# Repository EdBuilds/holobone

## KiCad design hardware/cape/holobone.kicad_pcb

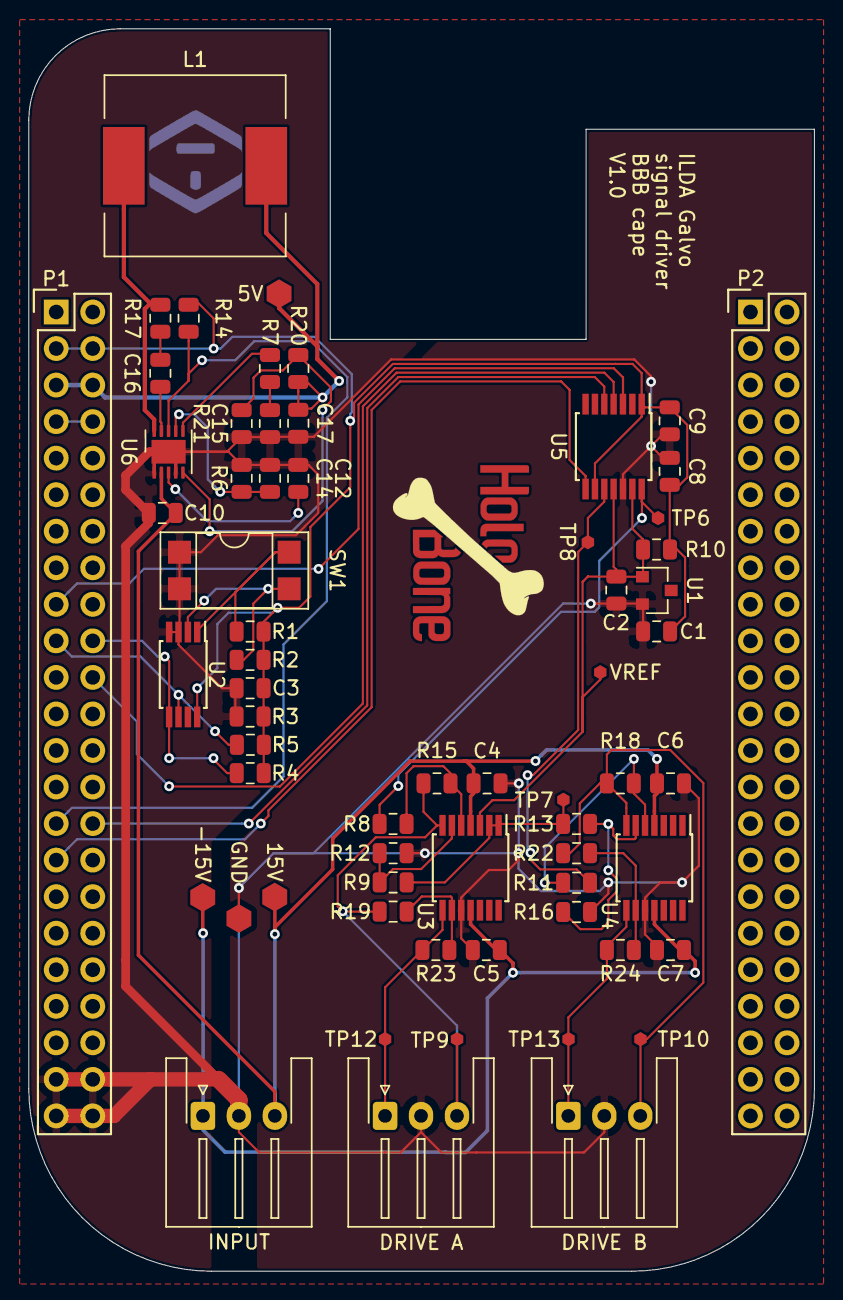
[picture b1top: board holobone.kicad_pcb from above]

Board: 2 copper layers, 54.6 x 86.4 mm, 65 parts (0 on the bottom side), 37 nets.

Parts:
5V, 15V: TestPoint; hex_test_pad_2mm
 : HoloBone_logo12.2x10.5mm
-15V: TestPoint; hex_test_pad_2mm
C1, C2, C3, C4, C5, C6, C7, C9, C16: 0.1uF; C_0805_2012Metric
C8: 4.7uF; C_0805_2012Metric
C10: 10uF; C_0805_2012Metric
C12: 3.3uF; C_0805_2012Metric
C14: 22nF; C_0805_2012Metric
C15: 1000 pF; C_0805_2012Metric
C17: 2.2uF; C_0805_2012Metric
DRIVE A: Conn_01x03; JST_XH_S3B-XH-A-1_1x03_P2.50mm_Horizontal
DRIVE B: Conn_01x03; JST_XH_S3B-XH-A-1_1x03_P2.50mm_Horizontal
GND: TestPoint; hex_test_pad_2mm
INPUT: Conn_01x03; JST_XH_S3B-XH-A-1_1x03_P2.50mm_Horizontal
L1: 47 uH; L_12x12mm_H8mm
P1, P2: BeagleBone_Black_Header; Socket_BeagleBone_Black
R1, R2, R3: 4.75K; R_0805_2012Metric
R4, R5: 5.6K; R_0805_2012Metric
R6: 4.7M; R_0805_2012Metric
R7: 10K; R_0805_2012Metric
R8, R11: 3.9K; R_0805_2012Metric
R9, R13, R19, R22, R23, R24: 16.2K; R_0805_2012Metric
R10: 2K; R_0805_2012Metric
R12, R16: 11.3K; R_0805_2012Metric
R14: 16.9K; R_0805_2012Metric
R15, R18: 18.7K; R_0805_2012Metric
R17: 10R; R_0805_2012Metric
R20: 147K; R_0805_2012Metric
R21: 28K; R_0805_2012Metric
SW1: SW_DIP_x02; DIP-4_W7.62mm_SMDSocket_SmallPads
TP6, TP7, TP8, TP9, TP10, TP12, TP13: TestPoint; hex_test_pad_1mm
U1: LM4040DBZ-2.0; SOT-23
U2: CAT24C256; TSSOP-8_4.4x3mm_P0.65mm
U3, U4: TL084; TSSOP-14_4.4x5mm_P0.65mm
U5: MCP4922-EST; TSSOP-14_4.4x5mm_P0.65mm
U6: ST1S50; DFN-10-1EP_3x3mm_P0.5mm_EP1.65x2.38mm
VREF: TestPoint; hex_test_pad_1mm

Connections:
+3V3: C1.2, C3.1, C8.2, C9.2, P1.3, P1.4, R1.1, R2.1, R3.1, R4.1, R5.1, R10.1, R14.1, U2.8, U5.1, U5.9
+5V: 5V.1, C17.2, L1.2, P1.5, P1.6, R20.1
+15V: 15V.1, C4.2, C6.2, C10.2, INPUT.3, U3.4, U4.4, U6.2
-15V: -15V.1, C5.1, C7.1, INPUT.1, U3.11, U4.11
CS_DAC: P1.17, U5.3
GND: C1.1, C2.1, C3.2, C4.1, C5.2, C6.1, C7.2, C8.1, C9.1, C10.1, C12.1, C14.1, C15.1, C17.1, DRIVE A.2, DRIVE B.2, GND.1, INPUT.2, P1.43, P1.44, P1.45, P1.46, R3.2, R6.2, R12.2, R16.2, R21.2, SW1.1, SW1.2, U1.2, U2.3, U2.4, U3.10, U4.10, U5.12, U6.1, U6.4, U6.11
LDAC: P1.31, U5.8
MOSI: P1.30, U5.5
unnamed: C12.2, U6.3
unnamed: C14.2, R6.1, U6.7
unnamed: C15.2, R7.2
unnamed: C16.1, R17.1
unnamed: C16.2, U6.9
unnamed: DRIVE A.1, R23.2, TP12.1, U3.8
unnamed: DRIVE A.3, R15.2, R19.1, TP9.1, U3.7
unnamed: DRIVE B.1, R24.2, TP13.1, U4.8
unnamed: DRIVE B.3, R18.2, R22.1, TP10.1, U4.7
unnamed: L1.1, R17.2, U6.10
unnamed: R1.2, SW1.4, U2.1
unnamed: R2.2, SW1.3, U2.2
unnamed: R7.1, U6.6
unnamed: R8.1, TP6.1, U5.14
unnamed: R11.1, TP8.1, U5.10
unnamed: R11.2, R18.1, U4.5
unnamed: R9.2, R12.1, U3.6
unnamed: R9.1, R13.1, TP7.1, U3.1, U3.2
unnamed: R13.2, R16.1, U4.6
unnamed: R8.2, R15.1, U3.5
unnamed: R19.2, R23.1, U3.9
unnamed: R20.2, R21.1, U6.5
unnamed: R22.2, R24.1, U4.9
POWER_GOOD: P1.29, R14.2, U6.8
SCL: P1.19, R5.2, U2.6
SCLK: P1.22, U5.4
SDA: P1.20, R4.2, U2.5
SYS_5V: P1.7, P1.8
VREF: C2.2, R10.2, U1.1, U3.3, U5.11, U5.13, VREF.1

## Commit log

2020-03-06 Working svg tracer
2020-03-09 add kicad project
2020-03-09 Add eeprom to HW
2020-04-30 add schematics
2020-06-14 pcb prodiction
2020-06-19 SPI bitbanged
2020-06-28 I don't even know man
2020-06-30 Added visual debugging
2020-07-19 This is falling apart
2020-08-13 ctrlc and platform dependent compilation
2020-08-30 New svg parsing and tracing
    small improvements
2020-08-31 New main function
2020-11-28 second hardware revision schematics done
2020-12-13 Minor changes
2020-12-13 Add Jenkinsfile
2020-12-20 Add text renderer
2020-12-23 MVP of the asteroids game
2020-12-26 Working rocket server
2020-12-30 Add Frontend
2020-12-30 Add frontend to jenkinsfile
2020-12-30 disable wasm-opt
2020-12-30 Use nightly to build
2020-12-30 Fix clippy error
2020-12-31 clippy errors down to 80
2021-01-01 down to 33 warnings
2021-01-01 No clippy issues remaining
2021-01-01 cheeky rust formatting
2021-01-01 Fix arm build
2021-01-03 Working enum based api
2021-01-10 Working rocket server
    Add Frontend
    Add frontend to jenkinsfile
    disable wasm-opt
    Use nightly to build
    Fix clippy error
    Working enum based api
2021-01-10 Basic cross setup
    pulled gilrs out to be able to build locally again
